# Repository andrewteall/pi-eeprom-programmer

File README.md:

# __A Raspberry Pi GPIO EEPROM Writer and Reader__ 

A way to write Parallel and Serial EEPROMs using the Raspberry Pi GPIO pins.

## __Quick Start__

### __Building the Circuit__
Before reading or writing any EEPROM you have to build the apprpriate circuit to do so.

You'll need a breadboard, jumper wires, and a 40-pin connector and cable to attach to the GPIO pins of the Raspberry Pi and a way to connect the opposite end to the breadboard. I like using one of the many Raspberry Pi GPIO Breakout boards available.

__Serial I2C EEPROM Circuit__
```
            Raspberry Pi GPIO                         I2C DIP8 Serial EEPROM
            3V3  (1) (2)  5V                   GND <-  A0 | (1) (8) | VCC -> 3V3
 SDA 5 -> GPIO2  (3) (4)  5V                   GND <-  A1 | (2) (7) | WP  -> GPIO16 (36)
 SCL 6 -> GPIO3  (5) (6)  GND                  GND <-  A2 | (3) (6) | SCL -> GPIO2  (3)
          GPIO4  (7) (8)  GPIO14               GND <- GND | (4) (5) | SDA -> GPIO3  (5)
            GND  (9) (10) GPIO15
         GPIO17 (11) (12) GPIO18
         GPIO27 (13) (14) GND   
         GPIO22 (15) (16) GPIO23
            3V3 (17) (18) GPIO24
         GPIO10 (19) (20) GND   
          GPIO9 (21) (22) GPIO25
         GPIO11 (23) (24) GPIO8 
            GND (25) (26) GPIO7 
          GPIO0 (27) (28) GPIO1 
          GPIO5 (29) (30) GND   
          GPIO6 (31) (32) GPIO12
         GPIO13 (33) (34) GND   
         GPIO19 (35) (36) GPIO16 -> 7 WP
         GPIO26 (37) (38) GPIO20
            GND (39) (40) GPIO21
   ```

   __Parallel EEPROM Circuit__
```
 IC  |   Raspberry Pi GPIO      | IC  |        Pi  |  DIP28 Parallel EEPROM  |  Pi         | DIP24 Parallel EEPROM
          3V3  (1) (2)  5V            |  (7)  GPIO4 <-  A14  (1) (28) VCC  -> 5V           |
I/O3 -> GPIO2  (3) (4)  5V            | (11) GPIO17 <-  A12  (2) (27) /WE  -> GPIO14 (8)   |
I/O4 -> GPIO3  (5) (6)  GND           | (13) GPIO27 <-   A7  (3) (26) A13  -> GPIO15 (10)  | VCC -> 5V
A14 ->  GPIO4  (7) (8)  GPIO14 -> /WE | (15) GPIO22 <-   A6  (4) (25) A8   -> GPIO18 (12)  | 
          GND  (9) (10) GPIO15 -> A13 | (19) GPIO10 <-   A5  (5) (24) A9   -> GPIO23 (16)  | 
A12 -> GPIO17 (11) (12) GPIO18 -> A8  | (21)  GPIO9 <-   A4  (6) (23) A11  -> GPIO24 (18)  | /WE -> GPIO14 (8)
 A7 -> GPIO27 (13) (14) GND           | (23) GPIO11 <-   A3  (7) (22) /OE  -> GPIO25 (22)  | 
 A6 -> GPIO22 (15) (16) GPIO23 -> A9  | (27)  GPIO0 <-   A2  (8) (21) A10  -> GPIO8  (24)  | 
          3V3 (17) (18) GPIO24 -> A11 | (29)  GPIO5 <-   A1  (9) (20) /CE  -> GPIO7  (26)  | 
 A5 -> GPIO10 (19) (20) GND           | (31)  GPIO6 <-   A0 (10) (19) I/O7 -> GPIO1  (28)  | 
 A4 ->  GPIO9 (21) (22) GPIO25 -> /OE | (33) GPIO13 <- I/O0 (11) (18) I/O6 -> GPIO12 (32)  | 
 A3 -> GPIO11 (23) (24) GPIO8  -> A10 | (35) GPIO19 <- I/O1 (12) (17) I/O5 -> GPIO16 (36)  | 
          GND (25) (26) GPIO7  -> /CE | (37) GPIO26 <- I/O2 (13) (16) I/O4 -> GPIO3  (38)  | 
 A2 ->  GPIO0 (27) (28) GPIO1  -> I/O7|          GND <- GND (14) (15) I/O3 -> GPIO2  (40)  | 
 A1 ->  GPIO5 (29) (30) GND           |
 A0 ->  GPIO6 (31) (32) GPIO12 -> I/O6| 
I/O0 ->GPIO13 (33) (34) GND           |
I/O1 ->GPIO19 (35) (36) GPIO16 -> I/O5| 
I/O2 ->GPIO26 (37) (38) GPIO20        | 
          GND (39) (40) GPIO21 ->     | 
   ```

   Alternatively a pcb can be ordered from any of the various manufacturers from the zipped gerbers contained in `hardware/manufacturing/pi-eeprom-programmer-v.v.v.zip`.

### __Installation and Raspberry Pi Setup__

If you plan to use serial EEPROMs you'll need to setup I2C on the Raspberry Pi. [Adafruit](https://learn.adafruit.com/adafruits-raspberry-pi-lesson-4-gpio-setup/configuring-i2c) has a great tutorial. Typically, if you're just using parallel EEPROM's then you can proceed to the next step. However, if the `libgpiod2` and `libgpiod-dev` packages are not installed on your Raspberry Pi you will need to to install them.

Download and compile the programmer software
```
git clone git@github.com:andrewteall/pi-eeprom-programmer.git
cd pi-eeprom-programmer/software
make
```

Install piepro

```
make install
```

That's it. You should be able to start reading and writing EEPROMs.

### __Installing the IC__
If you've recreated the circuit exactly from above or are using the pcb the IC should be installed so that the bottom left pin of the IC is aligned to the bottom left of the circuit.

### __Reading from an EEPROM__

To read an EEPROM, after building the circuit and inserting the IC, run the command
```sh
piepro -d -m EEPROM_MODEL
```
Where EEPROM_MODEL is typically the IC's part number such as at28c64, xl2816, at24c02, etc... This will dump the EEPROM's contents to standard out in a pretty format. If you wish to start or limit the addresses dumped you may specify the `-s ADDRESS` or `-l ADDRESS` flags respectively.

### __Writing to an EEPROM__

To write to an EEPROM, after building the circuit and inserting the IC, run the command
```sh
piepro -w file.bin -m EEPROM_MODEL
```
To compare you EEPROM to the file after writing, run the command

```sh
piepro -c file.bin -m EEPROM_MODEL
```
Where EEPROM_MODEL is typically the IC's part number such as at28c64, xl2816, at24c02, etc...

#### __A Quick Note About EEPROM Voltages__
Most modern EERPOMs will work but if you're using an obscure EEPROM you need to makes sure it can operate on 5v Vcc and 3.3v levels if it's a parallel EEPROM and 3.3v Vcc and 3.3v levels if it's a serial EEPROM.

## __Command Line Options__
```
Usage: piepro [options]
Options:
 -c FILE,   --compare FILE  Compare FILE and EEPROM and print number of differences.
            --chipname      Specify the chipname to use. Default: gpiochip0
 -d [N],    --dump [N]      Dump the contents of the EEPROM, 
                            0=PRETTY_WITH_ASCII, 1=BINARY, 2=TEXT, 3=LABELED, 4=PRETTY. Default: PRETTY_WITH_ASCII
 -e [N],    --erase [N]     Erase eeprom with specified byte. Default: 0xFF
 -f,        --force         Force writing of every byte instead of checking for existing value first.
 -id,       --i2c-device-id The address id of the I2C device.
 -h,        --help          Print this message and exit.
 -l N,      --limit N       Specify the maximum address to operate.
 -m MODEL,  --model MODEL   Specify EERPOM device model. Default: AT28C16.
            --no-validate-write 
                            Do not perform a read directly after writing to verify the data was written.
 -r [N],    --read [N]      Read the contents of the EEPROM, 
                            0=PRETTY_WITH_ASCII, 1=BINARY, 2=TEXT, 3=LABELED, 4=PRETTY. Default: PRETTY_WITH_ASCII
 -rb N,     --read-byte ADDRESS 
                            Read From specified ADDRESS.
 -q [N],     --quick [N]    Operates on N bytes at once for reads. Page Size if unspecified or writes. 
                            Implied --force and --no-validate-write.
 -s N,      --start N       Specify the minimum address to operate.
 -t,        --text          Interpret file as a text. Default: binary
                            Text File format:
                            [00000000]00000000 00000000
 -v N,      --v[vvvv]       Set the log verbosity to N, 0=OFF, 1=FATAL, 2=ERROR, 3=WARNING, 4=INFO, 5=DEBUG 6=TRACE. Default: WARNING
            --version       Print the piepro version and exit.
 -w FILE,   --write FILE    Write EEPROM with specified file.
 -wb ADDRESS DATA, --write-byte ADDRESS DATA 
                            Write specified DATA to ADDRESS.
 -wd [N],   --write-delay N Enable write delay. N Number of microseconds to delay between writes.
 -y,        --yes           Automatically answer Yes to write or erase EEPROM.

 Supported and tested Models:
        Note that the program may work if your EEPROM uses a similar pinout and
        voltages to the ones listed.
 Model       Size(B)  Addr Len  Data Len   Write Cycle(uS)  Page Size(B) Address Size(B)
----------------------------------------------------------------------------------------
xl2816        2048       11         8          10000            16             0
xl28c16       2048       11         8          10000            16             0
at28c16       2048       11         8           5000            16             0
at28c64       8192       13         8          10000            16             0
at28c256     32768       15         8           1000            64             0
at24c01        128        7         8           5000             8             1
at24c02        256        8         8           5000             8             1
at24c04        512        9         8           5000            16             2
at24c08       1024       10         8           5000            16             2
at24c16       2048       11         8           5000            16             2
at24c32       4096       12         8           5000            32             2
at24c64       8192       13         8           5000            32             2
at24c128     16384       14         8           5000            64             2
at24c256     32768       15         8           5000            64             2
at24c512     65536       16         8           5000           128             2
 ```

 ## __Features, Bugs, and Contributing__
If there's anything you'd like to add or find a bug please open an [issue](https://github.com/andrewteall/pi-eeprom-programmer/issues). If you'd like to implement those chages yourself please feel free to open a PR or fork the repository and make it your own.

## __License__
This repository is licensed under the [MIT-0 License](LICENSE) for everything not contained in the hardware folder and it's sub folders. For all files and folders in the hardware folder and it's sub folders, they are licensed under [CC0](https://creativecommons.org/publicdomain/zero/1.0/). You are free to use, modify, and distribute the project according to the terms of these licenses.

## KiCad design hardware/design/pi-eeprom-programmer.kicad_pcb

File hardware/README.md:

# __A Raspberry Pi GPIO EEPROM Writer and Reader__ 

A way to write Parallel and Serial EEPROMs using the Raspberry Pi GPIO pins.

## __Introduction__
The Raspberry Pi EEPROM Programmer is a hardware project that facilitates the programming and updating of EEPROMs using a Raspberry Pi. Instead of having to wire a circuit up on a bread board, the idea is just to be able to plug the EEPROM in to the pcb via a socket of some sort and then plug the pcb into the Raspberry Pi's GPIO pins.

This README provides an overview of the features, hardware design, and usage instructions for the Raspberry Pi EEPROM Programmer.

## __Folder Structure__

### Hardware Design
The hardware design files for the Raspberry Pi EEPROM Programmer can be found in the [hardware](../hardware/design/) directory of this repository. The design includes:

- **Kicad Project File:** The Kicad 6 project file to open the designs.
- **Schematic:** The schematic diagram detailing the connections between components and the Raspberry Pi.
- **PCB Layout:** The PCB layout design files used for creating the physical printed circuit board.

The hardware design is created using industry-standard design software, and you are encouraged to review, modify, or contribute to the design according to your needs.

### Manufacturing
The manufacturing files for the Raspberry Pi EEPROM Programmer can be found in the [manufacturing](../hardware/manufacturing/) directory of this repository.

- **Bill of Materials:** A list of all components required for building the programmer.
- **Gerbers:** Ready to build design files for the programmer.

### Repository Related Files

- **.README.md:** Resource on how to build, use, and design this hardware.
- **.gitignore:** Hardware specific gitignore for this repository.

## __Design Updates to the Hardware/Contributing__
Starting with version 1.0.0 I have tried not to have any breaking changes which should be very easy given such simple hardware. 
If you want to contribute and make any changes to this repo please ensure that you don't break any backwards compatibility to the hardware unless you plan on forking it and making it your own. When making non-breaking minor changes to the design please use a branch with the next minor version(1.+.0) or next patch version(1.x.+) and update the schematic and pcb accordingly.

## __Building the Hardware in Kicad__
When generating the appropriate gerber and drill files they should go in the [gerbers](./manufacturing/gerbers/) folder. Any new version should provide a zipped file in [manufacturing](./manufacturing/) folder containing all the build files and replacing the old version. 
```
zip -j manufacturing/pi-eeprom-programmer-$(git rev-parse --abbrev-ref HEAD).zip manufacturing/gerbers/*
```
This should make it easy to upload the design to the pcb manufacturers. The defaults in Kicad should befine to generate gerbers and drill files only the output directory should have to be changed.

## __BOM__
| ID | Designator | Package                            | Quantity |         Designation         |       Part Number/Link      |
|:--:|:----------:|------------------------------------|:--------:|-----------------------------|:---------------------------:|
| 1  | J1         | PinSocket_2x20_P2.54mm_Horizontal  |    1     | Raspberry Pi GPIO Connector |  [SFH11-PBPC-D20-RA-BK](https://www.digikey.com/en/products/detail/sullins-connector-solutions/SFH11-PBPC-D20-RA-BK/1990101)  |
| 2  | U1         | DIP-28_W15.24mm_Socket             |    1     | ZIF Socket                  |  [28-6554-11](https://www.digikey.com/en/products/detail/aries-electronics/28-6554-11/27594)                                  |
| 3  | U2         | DIP-8_W7.62mm_Socket               |    1     |                             |                                                                                                                               |
| 4  | J2         | PinHeader_1x03_P2.54mm_Vertical    |    1     | Conn_01x03                  |  [TS-103-G-A](https://www.digikey.com/en/products/detail/samtec-inc/TS-103-G-A/1105459)                                       |
| 5  | *          | Conn_Jumper_Shorting               |    1     | *                           |  [QPC02SXGN-RC](https://www.digikey.com/en/products/detail/sullins-connector-solutions/QPC02SXGN-RC/2618262)                                       |

\* The Jumper Shunt is not listed anywhere in the schematic

__Notes:__
* U2 is not required unless you are not using the ZIF Socket or 28-Pin IC Socket in which case an 8-Pin IC Socket may be used.
* Similarly U1 may be substituted for a less expensive 28-Pin IC Socket.
* In certain cases if the ZIF socket is not used both the 28-Pin Socket and 8-Pin Socket may be used at the same time.
* All the parts can be found on via other sources so feel free to find them where they are the cheapest.

## __Assembling the PCB__
There are a very low number of components on the board and assembly is straight forward. One of the biggest options you have is the type of socket used. The BOM includes a Universal ZIF Socket(U1) that allows for plugging in both narrow and wide ICs, however a standard 28-Pin Wide DIP Socket(U1) can be used if you only need to program wide chips or an 8-Pin DIP Socket(U2) can be used for small serial EEPROMs. You can use either or, with a little encouragement, have both sockets in place at the same time. This is much cheaper than using the ZIF sockets but not as elegant(or as good for the IC Pins). 

J2 is a 1x3 Pin Header meant to be used with a shunt jumper to select between the different types of EEPROMs, 24-Pin or 28-Pin Parallel EEPROMS or 8 Pin Serial EEPROMs. You can also install a small SPDT sliding switch in place of the Pin Headers and the serial programming will work in either position.

J1 should be right angle 40-Pin connector. If you use a standard vertical 40-Pin Connector it will orient the EEPROM Programmer vertical/perpendicular to a Pi 400 and parallel and updside down to a standard Pi 4.

While I've included sources for all the parts feel free to use your own or source them from wherever you like or can find them cheapest. I've used a number of combinations of different components in testing and they've all worked fine.

Start by install the Sockets(U1/U2)(smallest first if you are trying to use both). Then install the Pin Header(JP2) and add your jumper shunt. Finally, install the right angle 40-Pin Connector.

## __Installation/Usage__
The Pi EEPROM Programmer should plug right into the GPIO Pins of the Raspberry Pi 4 or 400. Take note to make sure the pins are aligned correctly if you opt not to use a keyed 40-Pin connector.

For the Pi 400 the Programmer should stick out of the back of the case and for a Pi 4 the programmer should be vertical straight up assuming you are using the standard components and not others mentioned above.

You can then use the software provided in this repositor to read and write EEPROMs.

## __EEPROM Voltages__
See [A Quick Note About EEPROM Voltages](../README.md#a-quick-note-about-eeprom-voltages)

## __Features, Bugs, and Contributing__
If there's anything you'd like to add or find a bug please open an [issue](https://github.com/andrewteall/pi-eeprom-programmer/issues). If you'd like to implement those chages yourself please feel free to open a PR or fork the repository and make it your own.

## __License__
This hardware project is licensed under the [CC0](LICENSE). You are free to use, modify, and distribute the project according to the terms of the license.

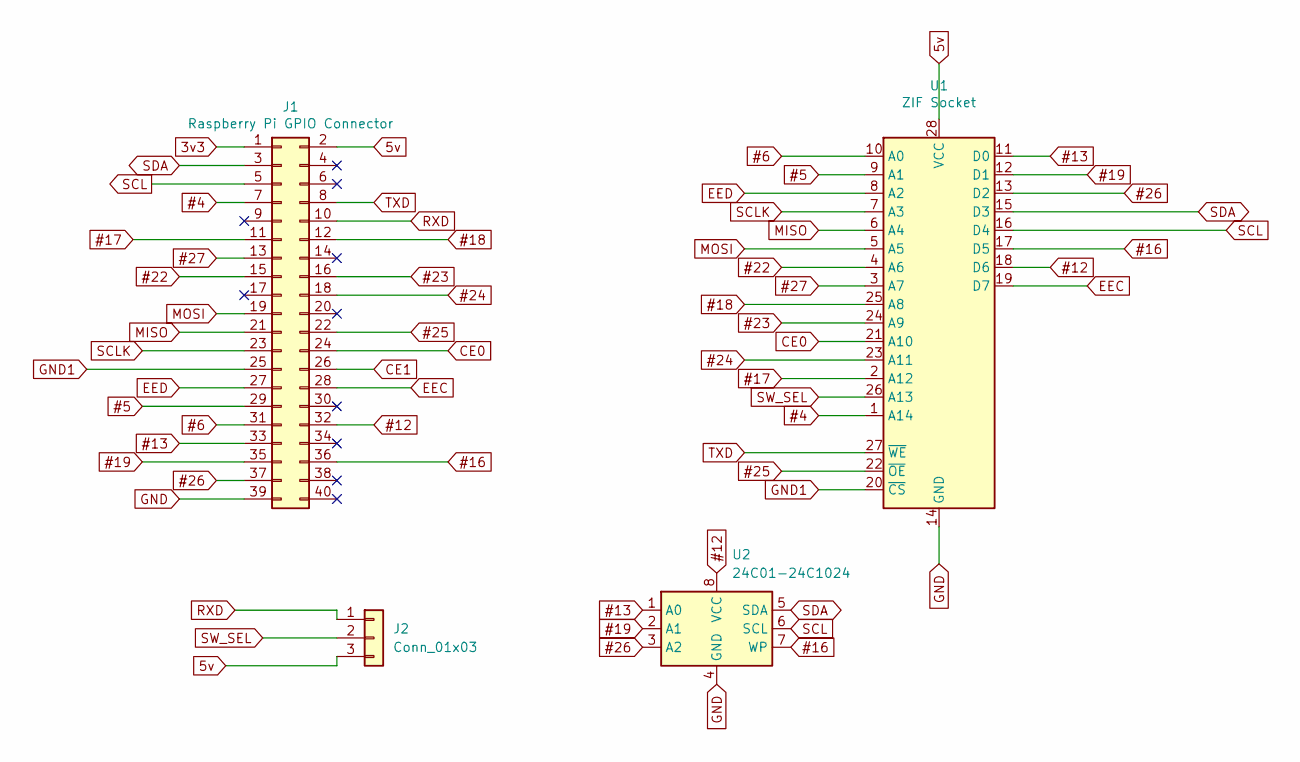
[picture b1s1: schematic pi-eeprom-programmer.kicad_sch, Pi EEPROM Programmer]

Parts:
J1: Raspberry Pi GPIO Connector; PinSocket_2x20_P2.54mm_Horizontal
J2: Conn_01x03; PinHeader_1x03_P2.54mm_Vertical
U1: ZIF Socket; DIP-28_W15.24mm_Socket
U2: 24C01-24C1024; DIP-8_W7.62mm_Socket

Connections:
3v3: J1.1
5v: J1.2, J2.3, U1.28 (VCC)
#4: J1.7, U1.1 (A14)
#5: J1.29, U1.9 (A1)
#6: J1.31, U1.10 (A0)
#12: J1.32, U1.18 (D6), U2.8 (VCC)
#13: J1.33, U1.11 (D0), U2.1 (A0)
#16: J1.36, U1.17 (D5), U2.7 (WP)
#17: J1.11, U1.2 (A12)
#18: J1.12, U1.25 (A8)
#19: J1.35, U1.12 (D1), U2.2 (A1)
#22: J1.15, U1.4 (A6)
#23: J1.16, U1.24 (A9)
#24: J1.18, U1.23 (A11)
#25: J1.22, U1.22 (~OE)
#26: J1.37, U1.13 (D2), U2.3 (A2)
#27: J1.13, U1.3 (A7)
CE0: J1.24, U1.21 (A10)
CE1: J1.26
EEC: J1.28, U1.19 (D7)
EED: J1.27, U1.8 (A2)
GND: J1.39, U1.14 (GND), U2.4 (GND)
GND1: J1.25, U1.20 (~CS)
MISO: J1.21, U1.6 (A4)
MOSI: J1.19, U1.5 (A5)
RXD: J1.10, J2.1
SCL: J1.5, U1.16 (D4), U2.6 (SCL)
SCLK: J1.23, U1.7 (A3)
SDA: J1.3, U1.15 (D3), U2.5 (SDA)
SW_SEL: J2.2, U1.26 (A13)
TXD: J1.8, U1.27 (~WE)

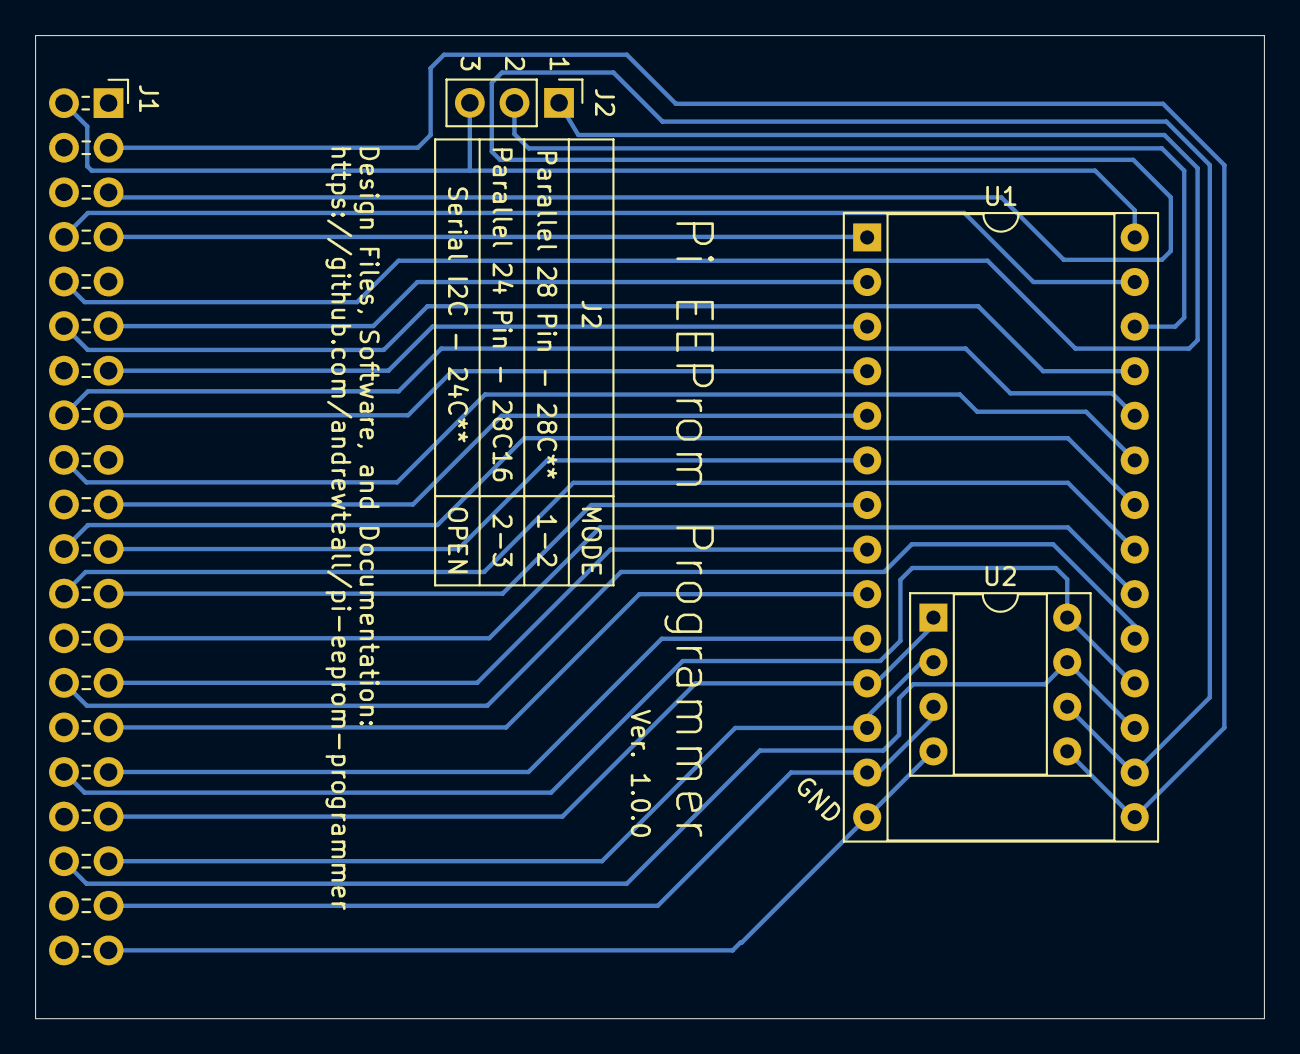
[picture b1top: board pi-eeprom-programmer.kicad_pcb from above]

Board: 2 copper layers, 70.0 x 56.0 mm, 4 parts (0 on the bottom side), 29 nets.

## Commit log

2022-09-12 Allow 2 byte address in Text File
2022-09-13 Move Address and Data pins to main from global
2022-09-13 Remove redudant text type specifier
2022-09-13 Make flags idempotent
2022-09-13 fix help return
2022-09-13 undo last commit
2022-09-13 Changed NUM_ADDRESS_PINS to 15
2022-09-13 Handle device type -t --type
2022-09-13 Remove backupWriter definition
2022-09-13 Cleanup Header and fix type handling
2022-09-14 Fix VCC Pin
2022-09-25 Working Programmer
2022-10-09 Cleanup
2022-10-10 change some log levels
2022-10-10 Add num address and data pins on chips
2022-10-11 Fix pin configuration for different chips
2022-10-12 More small fixes adjustments to write cycle time
2022-10-12 Serial support, write cycle delay adjust, i2c id
2022-10-12 Added non-CMOS eeprom support
2022-10-15 Cleanup and Better Docs
2022-10-15 Support start value for text files
2022-10-15 Support I2C IDs and WP
2022-10-15 More cleanup
2023-08-09 First pass adding hardware
2023-08-09 Remove fp-info-cache from tracking
2023-08-10 Added License
2023-08-10 *Broken* Restructured Software Project
2023-08-16 Switch from WiringPi to Chardev GPIO
2023-08-16 Updated board to reuse GPIO 2 & 3 for Chardev switch
2023-08-16 Added folder specific .gitignore for software and hardware
2023-08-17 Added make install, uninstall, and other make cleanup
2023-08-17 Main README updated
2023-08-19 Updated READMEs
2023-08-20 Software README and other README updates
2023-08-20 Removed add kicad prl file from source control
2023-08-21 Added kicad prl file to .gitignore
2023-08-21 Updated PCB to include spot for Serial EEPROM and updated README to reflect it
2023-08-21 Added Man Page
2023-08-21 Fix -t --text typo
2023-08-21 Updated MIT License reference to MIT-0
2023-08-21 Added name to License copyright
2023-08-21 Added --version flag
2023-08-21 Added updating and uninstallation to readme
2023-08-21 Added BOM and cleaned up schematic
2023-08-21 Added voltage info to hardware README
2023-08-21 Update Hardware folder structure and generate zip
2023-08-21 Added zip command to README
2023-08-21 change hardware to use CC0 and text accordingly
2023-08-22 fix typo on README
2023-08-22 Fix README path to zipped gerbers
2023-08-23 Software Refactor and cleanup
2023-08-23 Update software README about polling
2023-08-23 Fixes from GPIO tests
2023-08-24 Remove utils.h dependency from main
2023-08-24 Fix type
2023-08-24 Fix consts
2023-08-24 Encapsulate piepro parameters in gpioChip
2023-08-24 Fix when no dump format is specified.
2023-08-25 Fixed bad packaged zip
2023-08-25 Updated hardware README to correct zip command
2023-08-27 Account for greater than usable GPIO
2023-08-28 More gpio tests and fixes
2023-08-28 fix docs
2023-09-10 Major refactor
2023-09-11 Revamp to support multiple byte I2C addresses
2023-09-11 Remove unused lib
2023-09-11 Switch #define to enum in gpio.c
2023-09-11 gpio.c cleanup
2023-09-13 Refactor reading text files
2023-09-14 Fixed GPIO tests after refactor
2023-11-07 Added I2C Dummy write
2023-11-07 Move logging to its own source
2023-11-07 Fix gpioLines never being NULL check
2023-11-07 Remove unused RoundUp function
2023-11-07 Cleanup main formatting and standard
2023-11-07 Fix ulog formatting
2023-11-07 Fix write cycle time to be used is polling is disabled
2023-11-07 Fix Parallel writes
2023-11-07 Fix high value address off by 1 error
2023-11-07 Added how many bytes were written during write
2023-11-07 Better messages when performing an action
2023-11-08 Added nothing as an option for main
2023-11-08 Added Nothing options to main
2023-11-08 Handle parameter switch segfault when last argument
2023-11-08 Updated and corrected help docs
2023-11-08 Cleanup and formatting
2023-11-08 Hex format on address out of Range
2023-11-08 Handle overflow string to num conversion
2023-11-08 Move version to piepro files
2023-11-08 ULog Use fprintf instead of printf
2023-11-08 Utils binary number format check
2023-11-08 Fixed reading past end of file when smaller than EEPROM
2023-11-08 README update
2023-11-09 Exit if I2C cannot be setup
2023-11-09 Move I2C setup to after pins are configured
2023-11-09 Fix ulog comment typo
2023-11-09 Remove unused gpiod lib from gpio.h
2023-11-09 Cleanup GPIO comments
2023-11-09 Update Docs
2023-11-09 Fix multibyte I2C addresses and data sizings
2023-11-09 List all supported devices and parameters
2023-11-09 Enable Parallel EEPROM Polling
2023-11-09 Fix str2bin error messages printing when not supposed to
2023-11-13 Change Utils to use C library functions instead of bespoke ones.
2023-11-13 Fixed Data sizings for parallel EEPROMs
2023-11-13 Updated EEPROM read options
2023-11-13 Fix writing and comparing text files
2023-11-13 Switch logging to stderr
2023-11-13 Fix binary text export to be used with program
2023-11-14 Added set defualts to piepro.h
2023-11-14 Erase EEPROM options
2023-11-14 Fixed numBytesToRead in gpio for readI2C
2023-11-15 Update quirks on why paging isn't implemented
2023-11-15 Added --quick CLI flag and added quick option to erasure
2023-11-16 Add quick option to all writeable functions
2023-11-16 Added quick actions
2023-11-16 Fixed parallel bulk write
2023-11-16 Better error handling for main
2023-11-16 Better log message when quick compare doesn't match
2023-11-16 Added Shared library option
2023-11-17 Added readChunk option. Fixed reading past end of file
2023-11-17 Added -y --yes options to not prompt user
2023-11-17 Handle userPrompt option in main
2023-11-17 Fixed user prompt
2023-11-17 Cleaned up eraseEEPROM and added -y --yes option
2023-11-17 Cleanup printEEPROM added return val and fixed printing
2023-11-17 Cleanup Compare and write files
2023-11-17 Cleanup read and writ bytes
2023-11-17 cleanup cli options
2023-11-17 Move setPinLevel to setBytesI2C and getBytesI2C
2023-11-17 Cleanup Internal functions. Make get and set bytes use the same format
2023-11-19 log level eval fix
2023-11-19 Fix EOF not detected
2023-11-20 remove char cast for EOF
2023-11-21 Add byte read counter to text file actions
2023-11-21 Added page sizes and 0'd address size for parallel EEPROMs for quick writes
2023-11-25 Better Makefile with incremental builds
2023-11-26 Updated model map output for help
2023-11-26 Fix begin var not error with clang
2023-11-28 Fix quick write byte error
2023-11-28 Add TRACE log level
2023-11-28 Fix Clang fgetc error with char
2023-11-28 Fix Clang Case Statment errors
2023-11-28 Made test_clean not run after every test
2023-11-29 Fix Quick byte reads
2023-11-29 Re-Fix Quick byte read
2023-11-30 Fix text file writing and matching with negative number
2023-12-01 Fix duplicate byte read increments
2023-12-02 Fixed Not Quick reading num bytes
2023-12-02 Make PArity between get and set bytes parallel
2023-12-03 Added Pretty Print with ASCII option
2023-12-04 Change MODEL_TYPE to EEPROM_MODEL
2023-12-04 Revert "Change MODEL_TYPE to EEPROM_MODEL"
    This reverts commit 8c4d5954264a56c5535154752066bb36ff8f59c3.
2023-12-04 Update test runner
2023-12-04 Remove Default EEPROM
2023-12-04 Do not echo, echo statement
2023-12-04 Add 5 second timeout for write cyle polling
2023-12-04 Add Tests
2023-12-04 Track .zip files as binary in git
2023-12-04 Added Changelog
2023-12-04 Updated Version to 1.0.0 and generated new gerbers and zip
2023-12-04 Added TODO
